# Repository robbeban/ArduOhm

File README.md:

# ArduOhm
Roberto De Colle ver. 0.2
22.4.2024

Ohmmeter with automatic scale with Arduino

Use a voltage divider with known R1 and unknown Rx as in the picture.

<br>
Voltage on Rx is read from AnalogRead(A0) and converted in volt.

## Problem
With a fix R1 value (as 1K), the Rx value can be not accurate enough if Rx << R1 or Rx >> R1.
Therefore we need to change measurement scale changing the R1 value to be more similar to Rx value.<br>
## Solution
This can be made using 5 different R1 values and therefore 5 different measurement scale.

<br>

In pic you see 5 different "R1" resistor, 100, 1K, 10K, 100K, 1M.
5 Output pins of Arduino put 5V on the right R1, but just one output at a time can be on +5V otherwise all R1 will be 
in parallel as one resistor.
This is achieved setting all output pin as input pin (equivalent R is great and therefore no resistor is connected to 5V) and then just one pin at a time is setted as output e brought to +5V.
This make an automatic scale to use the suitable value for R1.
## Another problem
By measuring little values of Rx, the right scale has a R1 = 100; with little value of R1+Rx the current provided from Arduino is too high (ca. 50 mA or more).
Therefore we use a PNP transistor to request just a few little current from pin.
In order of turning on the PNP transistor, we need to set output pin LOW instead of HIGH as for the other scales.

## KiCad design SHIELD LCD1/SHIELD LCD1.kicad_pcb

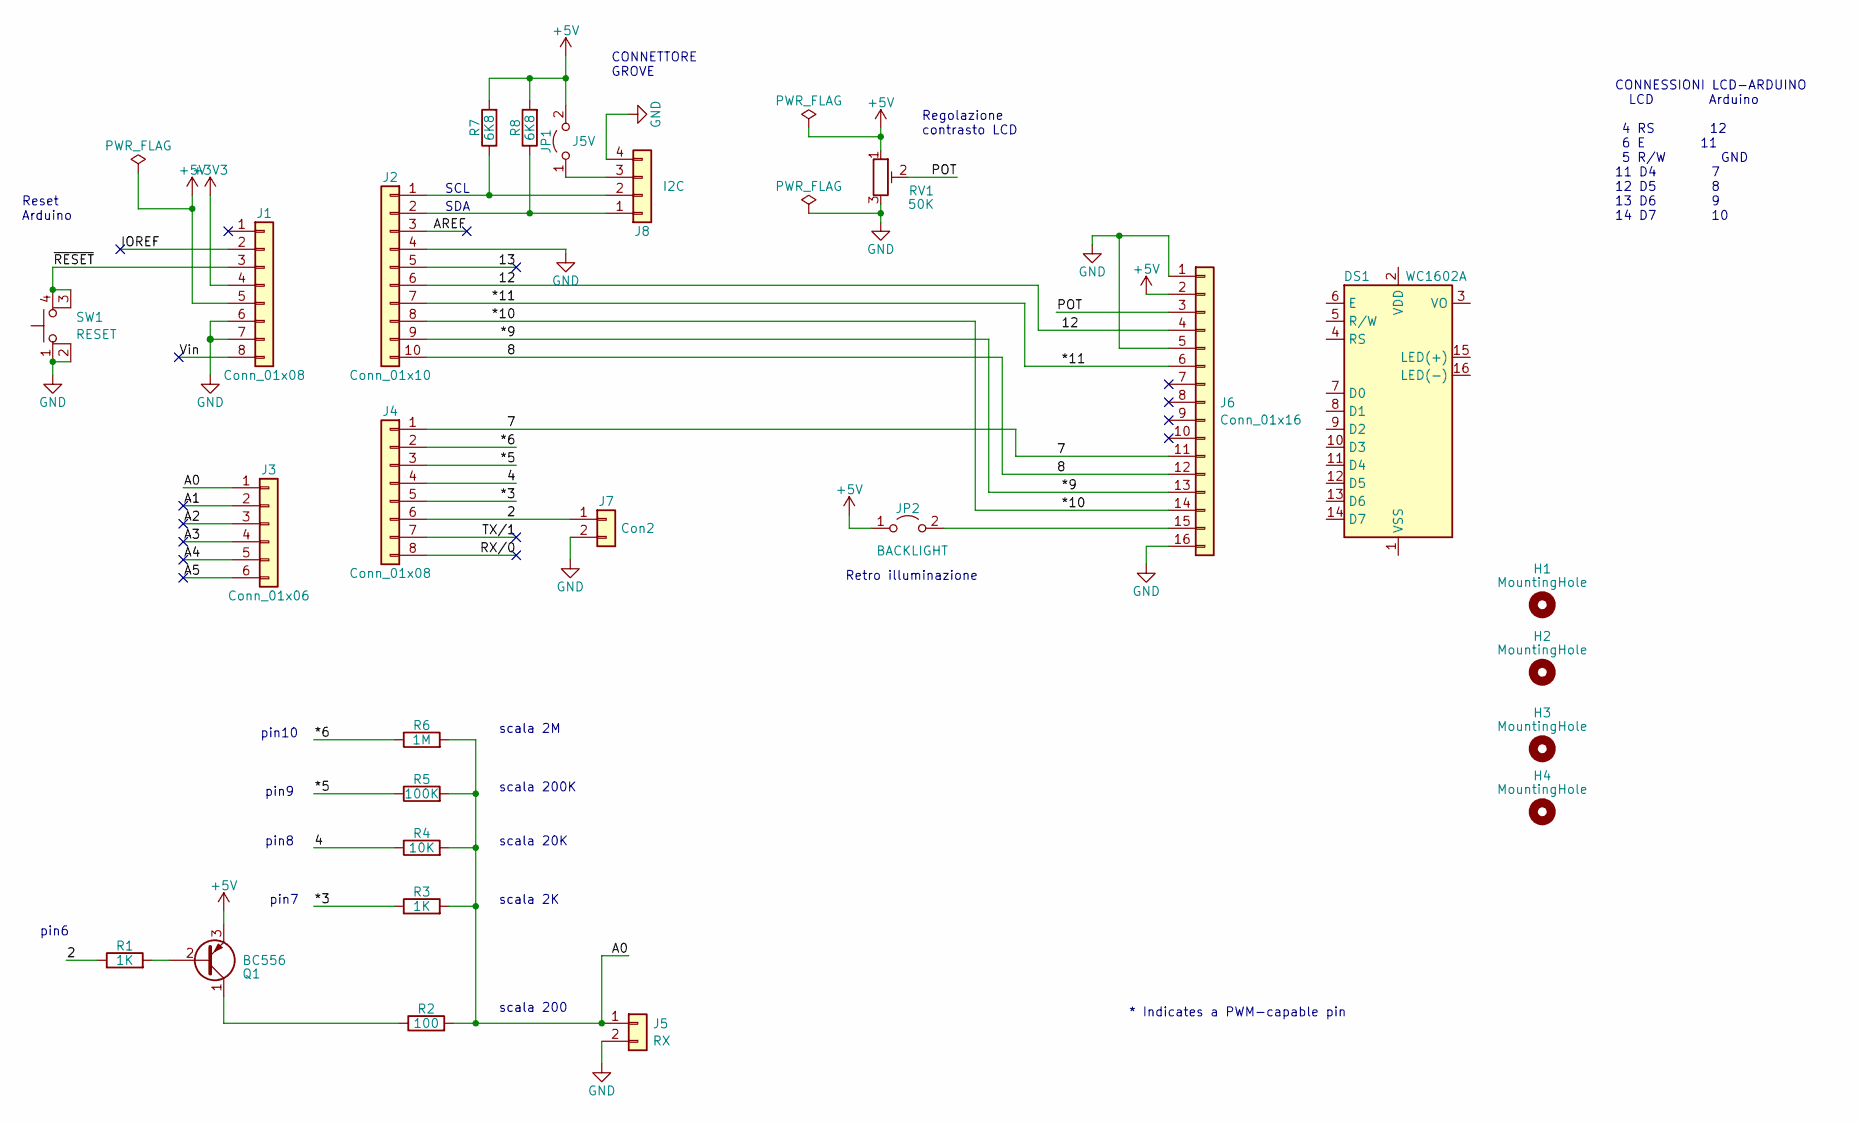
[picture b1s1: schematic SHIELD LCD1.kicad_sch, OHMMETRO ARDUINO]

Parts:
DS1: WC1602A
H1, H2, H3, H4: MountingHole; MountingHole_2.5mm
J1, J4: Conn_01x08; PinHeader_1x08_P2.54mm_Vertical
J2: Conn_01x10; PinHeader_1x10_P2.54mm_Vertical
J3: Conn_01x06; PinHeader_1x06_P2.54mm_Vertical
J5: RX; PinHeader_1x02_P2.54mm_Vertical
J6: Conn_01x16; PinHeader_1x16_P2.54mm_Vertical
J7: Con2; PinHeader_1x02_P2.54mm_Vertical
J8: I2C; NS-Tech_Grove_1x04_P2mm_Vertical
JP1: J5V; TestPoint_2Pads_Pitch2.54mm_Drill0.8mm
JP2: BACKLIGHT; TestPoint_2Pads_Pitch2.54mm_Drill0.8mm
Q1: BC556; TO-92_Inline_Wide
R1, R3: 1K; R_Axial_DIN0309_L9.0mm_D3.2mm_P12.70mm_Horizontal
R2: 100; R_Axial_DIN0411_L9.9mm_D3.6mm_P20.32mm_Horizontal
R4: 10K; R_Axial_DIN0309_L9.0mm_D3.2mm_P12.70mm_Horizontal
R5: 100K; R_Axial_DIN0309_L9.0mm_D3.2mm_P12.70mm_Horizontal
R6: 1M; R_Axial_DIN0309_L9.0mm_D3.2mm_P12.70mm_Horizontal
R7, R8: 6K8; R_Axial_DIN0309_L9.0mm_D3.2mm_P12.70mm_Horizontal
RV1: 50K; Potentiometer_Bourns_3296X_Horizontal
SW1: RESET; SW_PUSH_6mm_H4.3mm

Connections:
+3V3: J1.4
+5V: J1.5, J6.2, JP1.2 (B), JP2.1 (A), Q1.3 (E), R7.2, R8.2, RV1.1
/2: J4.6, J7.1, R1.1
/4: J4.4, R4.1
/7: J4.1, J6.11
/8: J2.10, J6.12
/12: J2.6, J6.4
/13: J2.5
/*3: J4.5, R3.1
/*5: J4.3, R5.1
/*6: J4.2, R6.1
/*9: J2.9, J6.13
/*10: J2.8, J6.14
/*11: J2.7, J6.6
/A0: J3.1, J5.1, R2.2, R3.2, R4.2, R5.2, R6.2
/A1: J3.2
/A2: J3.3
/A3: J3.4
/A4: J3.5
/A5: J3.6
/AREF: J2.3
/IOREF: J1.2
/POT: J6.3, RV1.2
/RX/0: J4.8
/TX/1: J4.7
/Vin: J1.8
/~RESET: J1.3, SW1.3 (K), SW1.4 (A)
GND: J1.6, J1.7, J2.4, J5.2, J6.1, J6.5, J6.16, J7.2, J8.4, RV1.3, SW1.1, SW1.2
unnamed: J2.1, J8.2, R7.1
unnamed: J2.2, J8.1, R8.1
unnamed: J6.15, JP2.2 (B)
unnamed: J8.3, JP1.1 (A)
unnamed: Q1.2 (B), R1.2
unnamed: Q1.1 (C), R2.1

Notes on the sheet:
SCL
Reset Arduino
SDA
scala 20K
pin6
scala 200K
Retro illuminazione
scala 200
pin7
scala 2K
* Indicates a PWM-capable pin
CONNESSIONI LCD-ARDUINO LCD Arduino 4 RS 12 6 E 11 5 R/W GND 11 D4 7 12 D5 8 13 D6 9 14 D7 10
pin10
scala 2M
CONNETTORE GROVE
pin9
Regolazione contrasto LCD
pin8

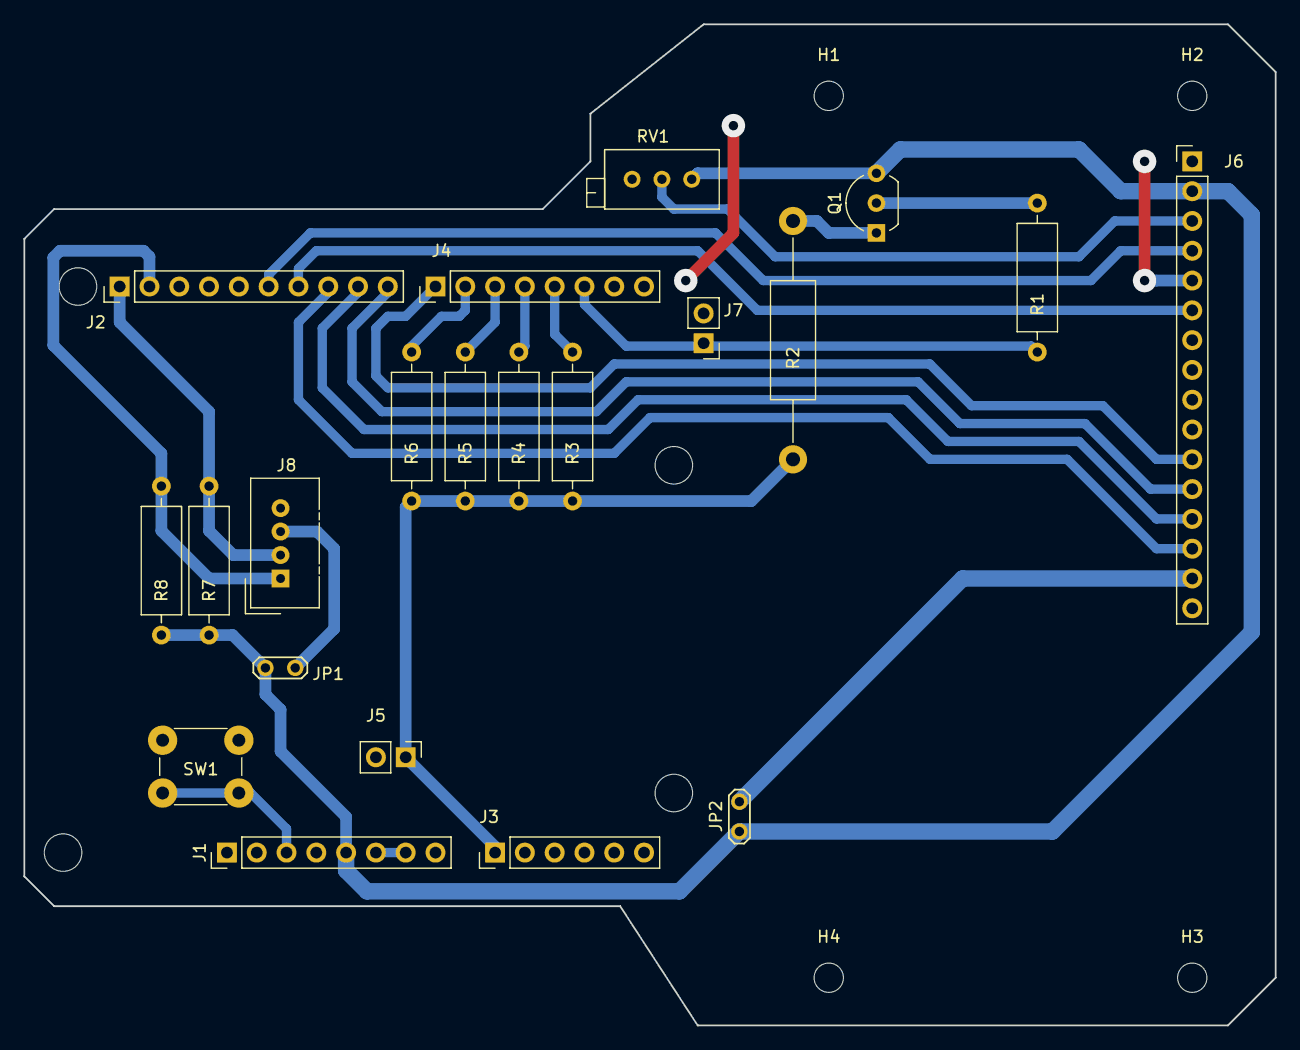
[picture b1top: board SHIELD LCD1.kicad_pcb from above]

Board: 2 copper layers, 106.7 x 85.3 mm, 29 parts (0 on the bottom side), 22 nets.

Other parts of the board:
MH1, MH2, MH3, MH4: MountingHole_3.2mm

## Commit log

2024-04-22 Add some pics
    voltage divider
2024-04-30 Add files via upload
    Ohmmetro2 prova scala automatica come provato a lezione il 30/4/24
    parte dalla scala 0 che corrisponde a R1=1M
2024-04-30 Add files via upload
    Documento Connessioni Arduino LCD
2024-04-30 Add files via upload
    Attenzione: i collegamenti sono corretti rispetto ai pin dell'LCD, come da file Kicad
2024-04-30 Add files via upload
    prova 1 con sala automatica
2024-05-07 Addd Arduino sketch definitivo
    ancora da provare V. 0.99
2024-05-07 Add foto ArduOhmmetro
    foto del prototipo finito V.0.99
2024-05-07 Add file
    Kicad file shield Arduohmmetro con LCD
    Attenzione: per Kicad vers. 7
2024-05-18 Add files via upload
    Sketch arduino di prova per trasmettere dati float via I2C da un Arduino master ad un altro slave
